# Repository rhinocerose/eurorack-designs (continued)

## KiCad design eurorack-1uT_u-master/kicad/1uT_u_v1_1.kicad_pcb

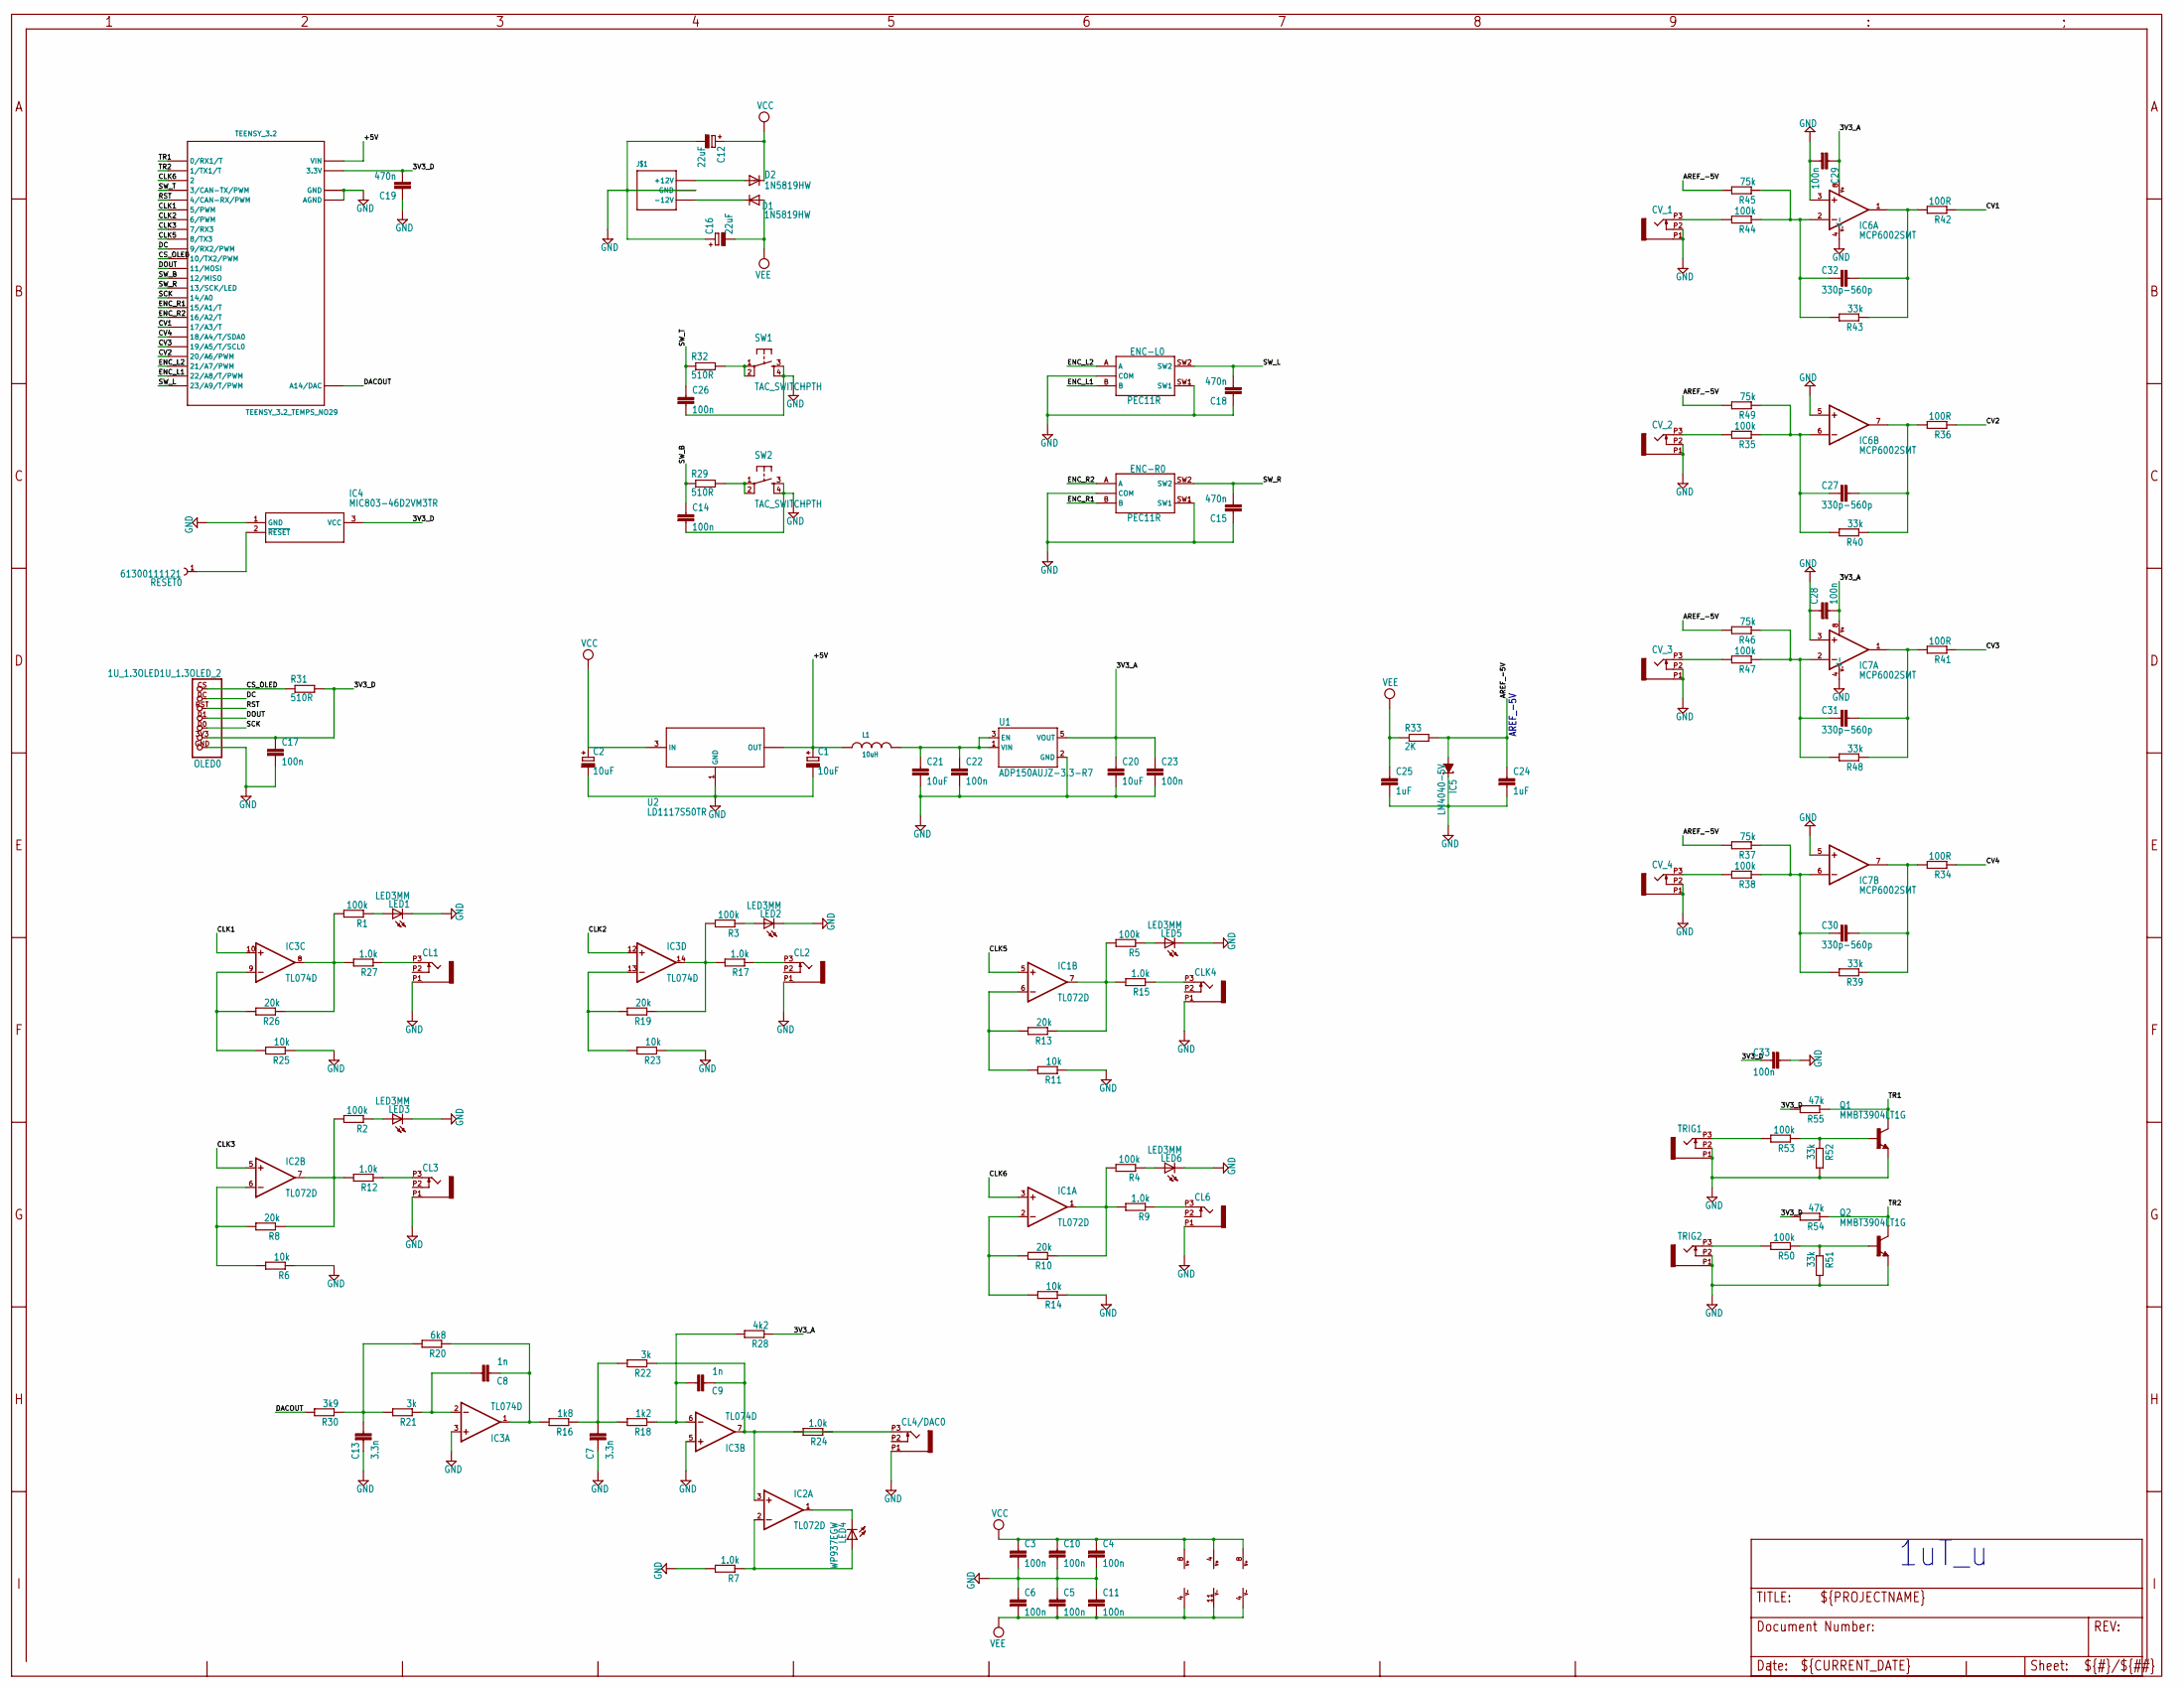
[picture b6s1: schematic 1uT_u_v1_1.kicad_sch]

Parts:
C1, C2: 10uF; PANASONIC_B
C3, C4, C5, C6, C10, C11, C14, C17, C22, C23, C26, C28, C29, C33: 100n; C0603
C7, C13: 3.3n; C0603
C8, C9: 1n; C0603
C12, C16: 22uF; PANASONIC_C
C15, C18, C19: 470n; C0603
C20, C21: 10uF; C1206K
C24, C25: 1uF; C0603
C27, C30, C31, C32: 330p-560p; C0603
CL1, CL2, CL3, CL4/DAC0, CL6: OG-PJ301_PJ301_THONKICONN; OG-PJ301_WQP_PJ_301M6_NO_HOLE
CLK4: OG-PJ301_PJ301_THONKICONN; OG-PJ301_WQP_PJ_301M6_NO_HOLE
CV_1, CV_2, CV_3, CV_4: OG-PJ301_PJ301_THONKICONN; OG-PJ301_WQP_PJ_301M6_NO_HOLE
D1, D2: 1N5819HW; DIODE_SOD123
ENC-L0: PEC11R; PEC11R-4XXXK-SXXXX
ENC-R0: PEC11R; PEC11R-4XXXK-SXXXX
IC1, IC2: TL072D; SO08
IC3: TL074D; SO14
IC4: MIC803-46D2VM3TR; SOT95P230X110-3N
IC5: LM4040-5V; DBZ_R-PDSO-G3
IC6, IC7: MCP6002SMT; SOIC8
J$1: POWER_SIMPLE10; POWER_10
L1: 10uH; WE-LQ_M
LED1, LED2, LED3, LED5, LED6: LED3MM
LED4: WP937EGW; LED3MM
OLED0: 1U_1.3OLED1U_1.3OLED_2; 1U_1.3OLED_2
Q1, Q2: MMBT3904LT1G; TRANSISTOR_SOT23-BEC
R1, R2, R3, R4, R5, R35, R38, R44, R47, R50, R53: 100k; R0603
R6, R11, R14, R23, R25: 10k; R0603
R7, R9, R12, R15, R17, R24, R27: 1.0k; R0603
R8, R10, R13, R19, R26: 20k; R0603
R16: 1k8; R0603
R18: 1k2; R0603
R20: 6k8; R0603
R21, R22: 3k; R0603
R28: 4k2; R0603
R29, R31, R32: 510R; R0603
R30: 3k9; R0603
R33: 2K; R0603
R34, R36, R41, R42: 100R; R0603
R37, R45, R46, R49: 75k; R0603
R39, R40, R43, R48, R51, R52: 33k; R0603
R54, R55: 47k; R0603
RESET0: 61300111121
SW1, SW2: TAC_SWITCHPTH; TACTILE-PTH
TEENSY_3.2: TEENSY_3.2_TEMPS_NO29
TRIG1, TRIG2: OG-PJ301_PJ301_THONKICONN; OG-PJ301_WQP_PJ_301M6_NO_HOLE
U1: ADP150AUJZ-3.3-R7; SOT95P280X100-5N
U2: LD1117S50TR; SOT223

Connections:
3V3_A: C20.1, C23.1, C28.2, C29.1, IC6.8 (V+), IC7.8 (V+), R28.1, U1.5 (VOUT)
3V3_D: C17.1, C19.2, C33.2, IC4.3 (VCC), OLED0.3V3, R31.2, R54.2, R55.2, TEENSY_3.2.3.3V
+5V: C1.+, L1.1, TEENSY_3.2.VIN, U2.2 (OUT), U2.4 (OUT)
AREF_-5V: C24.1, IC5.2 (A), R33.2, R37.2, R45.2, R46.2, R49.2
CLK1: IC3.10 (+IN), TEENSY_3.2.5 (5/PWM)
CLK2: IC3.12 (+IN), TEENSY_3.2.6 (6/PWM)
CLK3: IC2.5 (+IN), TEENSY_3.2.7 (7/RX3)
CLK5: IC1.5 (+IN), TEENSY_3.2.8 (8/TX3)
CLK6: IC1.3 (+IN), TEENSY_3.2.2
CS_OLED: OLED0.CS, R31.1, TEENSY_3.2.10 (10/TX2/PWM)
CV1: R42.1, TEENSY_3.2.17/A3 (17/A3/T)
CV2: R36.1, TEENSY_3.2.20/A6 (20/A6/PWM)
CV3: R41.1, TEENSY_3.2.19/A5 (19/A5/T/SCL0)
CV4: R34.1, TEENSY_3.2.18/A4 (18/A4/T/SDA0)
DACOUT: R30.2, TEENSY_3.2.RESET/DAC (A14/DAC)
DC: OLED0.DC, TEENSY_3.2.9 (9/RX2/PWM)
DOUT: OLED0.D1, TEENSY_3.2.11 (11/MOSI)
ENC_L1: ENC-L0.B, TEENSY_3.2.22/A8 (22/A8/T/PWM)
ENC_L2: ENC-L0.A, TEENSY_3.2.21/A7 (21/A7/PWM)
ENC_R1: ENC-R0.B, TEENSY_3.2.15/A1 (15/A1/T)
ENC_R2: ENC-R0.A, TEENSY_3.2.16/A2 (16/A2/T)
GND: C1.-, C2.-, C3.2, C4.2, C5.1, C6.1, C7.2, C10.2, C11.1, C12.-, C13.2, C14.2, C15.1, C16.+, C17.2, C18.1, C19.1, C20.2, C21.2, C22.2, C23.2, C24.2, C25.2, C26.2, C28.1, C29.2, C33.1, CL1.P1 (1), CL2.P1 (1), CL3.P1 (1), CL4/DAC0.P1 (1), CL6.P1 (1), CLK4.P1 (1), CV_1.P1 (1), CV_1.P2 (2), CV_2.P1 (1), CV_2.P2 (2), CV_3.P1 (1), CV_3.P2 (2), CV_4.P1 (1), CV_4.P2 (2), ENC-L0.C (COM), ENC-L0.SH1 (COM), ENC-L0.SH2 (COM), ENC-L0.SW1, ENC-R0.C (COM), ENC-R0.SH1 (COM), ENC-R0.SH2 (COM), ENC-R0.SW1, IC3.3 (+IN), IC3.5 (+IN), IC4.1 (GND), IC5.1 (C), IC6.3 (+IN), IC6.4 (V-), IC6.5 (+IN), IC7.3 (+IN), IC7.4 (V-), IC7.5 (+IN), J$1.3 (GND), J$1.4 (GND), J$1.5 (GND), J$1.6 (GND), J$1.7 (GND), J$1.8 (GND), LED1.K (C), LED2.K (C), LED3.K (C), LED5.K (C), LED6.K (C), OLED0.GND, Q1.E, Q2.E, R6.1, R7.2, R11.1, R14.1, R23.1, R25.1, R51.2, R52.2, SW1.3, SW1.4, SW2.3, SW2.4, TEENSY_3.2.AGND, TEENSY_3.2.GND, TRIG1.P1 (1), TRIG1.P2 (2), TRIG2.P1 (1), TRIG2.P2 (2), U1.2 (GND), U2.1 (GND)
unnamed: D2.A, J$1.9 (+12V), J$1.10 (+12V)
unnamed: C21.1, C22.1, L1.2, U1.1 (VIN), U1.3 (EN)
unnamed: CV_1.P3 (3), R44.2
unnamed: C32.2, IC6.2 (-IN), R43.2, R44.1, R45.1
unnamed: C32.1, IC6.1 (OUT), R42.2, R43.1
unnamed: R32.2, SW1.1, SW1.2
unnamed: CV_2.P3 (3), R35.2
unnamed: R29.2, SW2.1, SW2.2
unnamed: C27.2, IC6.6 (-IN), R35.1, R40.2, R49.1
unnamed: C27.1, IC6.7 (OUT), R36.2, R40.1
unnamed: CV_3.P3 (3), R47.2
unnamed: C31.2, IC7.2 (-IN), R46.1, R47.1, R48.2
unnamed: C31.1, IC7.1 (OUT), R41.2, R48.1
unnamed: CV_4.P3 (3), R38.2
unnamed: C30.2, IC7.6 (-IN), R37.1, R38.1, R39.2
unnamed: C30.1, IC7.7 (OUT), R34.2, R39.1
unnamed: R53.2, TRIG1.P3 (3)
unnamed: Q1.B, R52.1, R53.1
unnamed: R50.2, TRIG2.P3 (3)
unnamed: Q2.B, R50.1, R51.1
unnamed: CL1.P3 (3), R27.1
unnamed: CL3.P3 (3), R12.1
unnamed: IC1.6 (-IN), R11.2, R13.2
unnamed: IC1.7 (OUT), R5.2, R13.1, R15.2
unnamed: IC3.13 (-IN), R19.2, R23.2
unnamed: IC3.9 (-IN), R25.2, R26.2
unnamed: IC3.8 (OUT), R1.2, R26.1, R27.2
unnamed: CLK4.P3 (3), R15.1
unnamed: IC3.14 (OUT), R3.2, R17.2, R19.1
unnamed: CL2.P3 (3), R17.1
unnamed: IC2.6 (-IN), R6.2, R8.2
unnamed: IC2.7 (OUT), R2.2, R8.1, R12.2
unnamed: IC1.2 (-IN), R10.2, R14.2
unnamed: IC2.1 (OUT), LED4.K (C)
unnamed: IC2.2 (-IN), LED4.A, R7.1
unnamed: IC1.1 (OUT), R4.2, R9.2, R10.1
unnamed: CL6.P3 (3), R9.1
unnamed: D1.C, J$1.1 (-12V), J$1.2 (-12V)
unnamed: C13.1, R20.2, R21.2, R30.1
unnamed: C8.1, IC3.2 (-IN), R21.1
unnamed: C8.2, IC3.1 (OUT), R16.2, R20.1
unnamed: C7.1, R16.1, R18.2, R22.2
unnamed: C9.1, IC3.6 (-IN), R18.1, R28.2
unnamed: LED3.A, R2.1
unnamed: LED1.A, R1.1
unnamed: LED2.A, R3.1
unnamed: LED5.A, R5.1
unnamed: LED6.A, R4.1
unnamed: IC4.2 (~RESET), RESET0.1
RST: OLED0.RST, TEENSY_3.2.4 (4/CAN-RX/PWM)
SCK: OLED0.D0, TEENSY_3.2.14/A0
SW_B: C14.1, R29.1, TEENSY_3.2.12 (12/MISO)
SW_L: C18.2, ENC-L0.SW2, TEENSY_3.2.23/A9 (23/A9/T/PWM)
SW_R: C15.2, ENC-R0.SW2, TEENSY_3.2.13 (13/SCK/LED)
SW_T: C26.1, R32.1, TEENSY_3.2.3 (3/CAN-TX/PWM)
TR1: Q1.C, R55.1, TEENSY_3.2.0 (0/RX1/T)
TR2: Q2.C, R54.1, TEENSY_3.2.1 (1/TX1/T)
VCC: C2.+, C3.1, C4.1, C10.1, C12.+, D2.C, IC1.8 (V+), IC2.8 (V+), IC3.4 (V+), U2.3 (IN)
VEE: C5.2, C6.2, C11.2, C16.-, C25.1, D1.A, IC1.4 (V-), IC2.4 (V-), IC3.11 (V-), R33.1

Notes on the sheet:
1uT_u
AREF_-5V

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
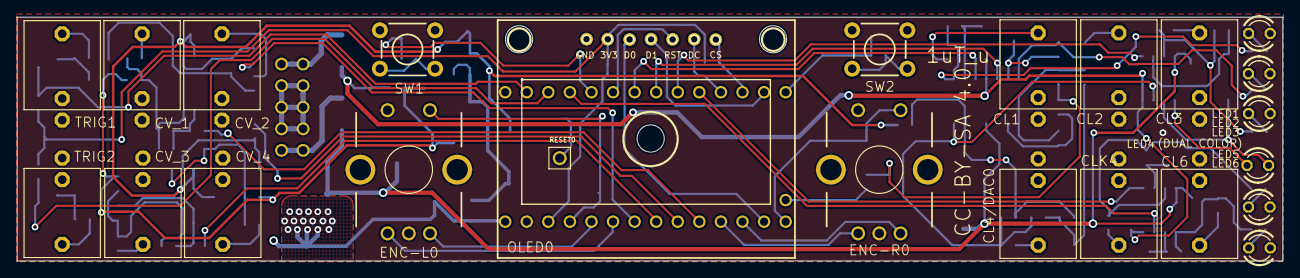
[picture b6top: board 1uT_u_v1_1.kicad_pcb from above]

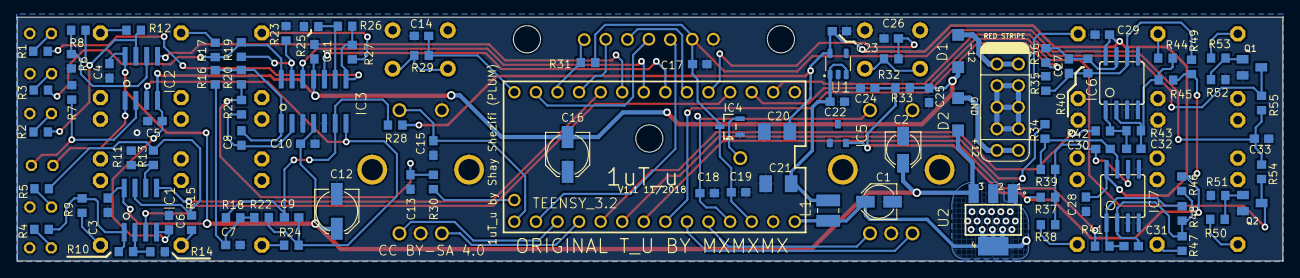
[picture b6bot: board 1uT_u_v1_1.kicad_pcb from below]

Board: 2 copper layers, 149.0 x 28.7 mm, 128 parts (104 on the bottom side), 83 nets.

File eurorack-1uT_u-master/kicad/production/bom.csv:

Designator,Footprint,Quantity,Value,LCSC Part #
"C1, C2",PANASONIC_B_334,2,10uF,
"C10, C11, C14, C17, C22, C23, C26, C28, C29, C3, C33, C4, C5, C6",C0603_348,14,100n,
"C12, C16",PANASONIC_C_334,2,22uF,
"C13, C7",C0603_348,2,3.3n,
"C15, C18, C19",C0603_348,3,470n,
"C20, C21",C1206K_348,2,10uF,
"C24, C25",C0603_348,2,1uF,
"C27, C30, C31, C32",C0603_348,4,330p-560p,
"C8, C9",C0603_348,2,1n,
"CL1, CL2, CL3, CL4/DAC0, CL6, CLK4, CV_1, CV_2, CV_3, CV_4, TRIG1, TRIG2",OG-PJ301_WQP_PJ_301M6_NO_HOLE,12,OG-PJ301_PJ301_THONKICONN,
"D1, D2",DIODE_SOD123,2,1N5819HW,
"ENC-L0, ENC-R0",PEC11R-4XXXK-SXXXX,2,PEC11R,
"IC1, IC2",SO08_262,2,TL072D,
IC3,SO14_262,1,TL074D,
IC4,SOT95P230X110-3N,1,MIC803-46D2VM3TR,
IC5,DBZ_R-PDSO-G3_387,1,LM4040-5V,
"IC6, IC7",SOIC8,2,MCP6002SMT,
J$1,POWER_10,1,POWER_SIMPLE10,
L1,WE-LQ_M_448,1,10uH,
"LED1, LED2, LED3, LED5, LED6",LED3MM_259,5,,
LED4,LED3MM_259,1,WP937EGW,
OLED0,1U_1.3OLED_2,1,1U_1.3OLED1U_1.3OLED_2,
"Q1, Q2",TRANSISTOR_SOT23-BEC,2,MMBT3904LT1G,
"R1, R2, R3, R35, R38, R4, R44, R47, R5, R50, R53",R0603_334,11,100k,
"R10, R13, R19, R26, R8",R0603_334,5,20k,
"R11, R14, R23, R25, R6",R0603_334,5,10k,
"R12, R15, R17, R24, R27, R7, R9",R0603_334,7,1.0k,
R16,R0603_334,1,1k8,
R18,R0603_334,1,1k2,
R20,R0603_334,1,6k8,
"R21, R22",R0603_334,2,3k,
R28,R0603_334,1,4k2,
"R29, R31, R32",R0603_334,3,510R,
R30,R0603_334,1,3k9,
R33,R0603_334,1,2K,
"R34, R36, R41, R42",R0603_334,4,100R,
"R37, R45, R46, R49",R0603_334,4,75k,
"R39, R40, R43, R48, R51, R52",R0603_334,6,33k,
"R54, R55",R0603_334,2,47k,
RESET0,61300111121_479,1,,
"SW1, SW2",TACTILE-PTH,2,,
TEENSY_3.2,TEENSY_3.2_TEMPS_NO29,1,TEENSY_3.2_TEMPS_NO29,
U1,SOT95P280X100-5N,1,ADP150AUJZ-3.3-R7,
U2,SOT223,1,LD1117S50TR,

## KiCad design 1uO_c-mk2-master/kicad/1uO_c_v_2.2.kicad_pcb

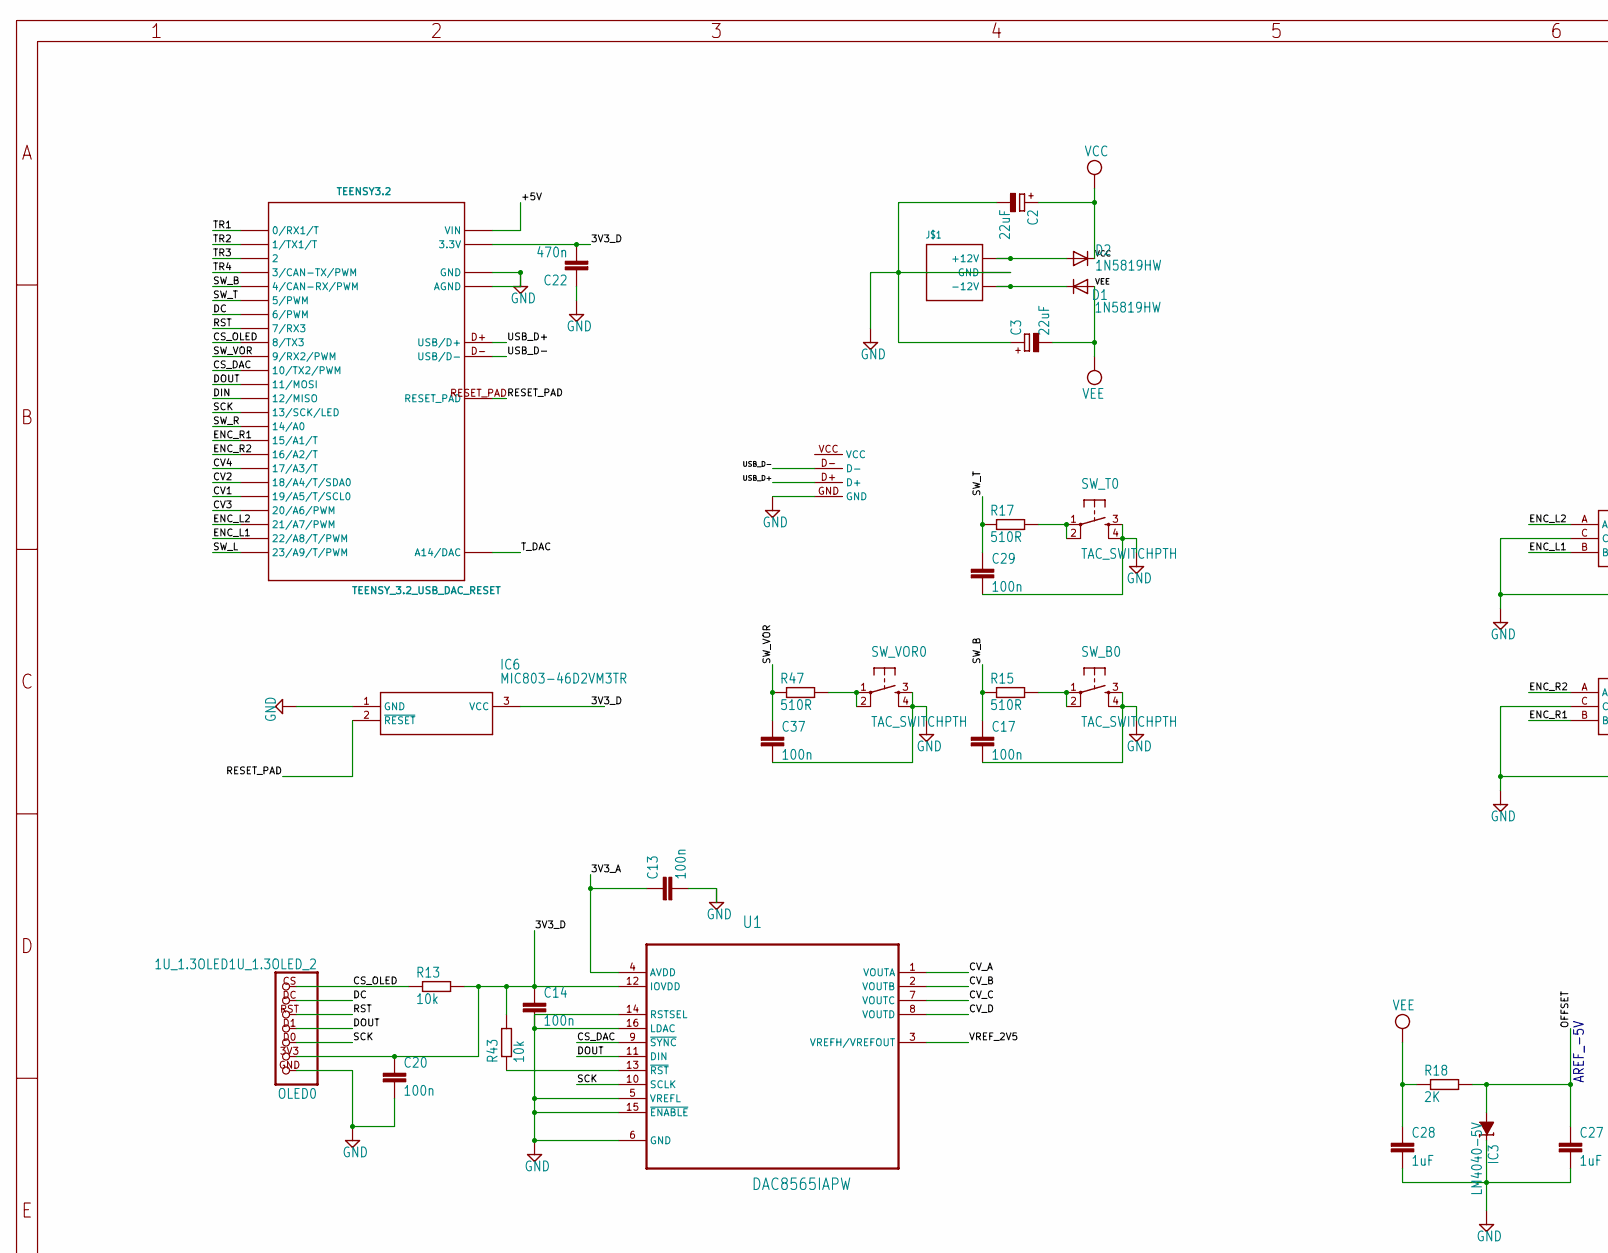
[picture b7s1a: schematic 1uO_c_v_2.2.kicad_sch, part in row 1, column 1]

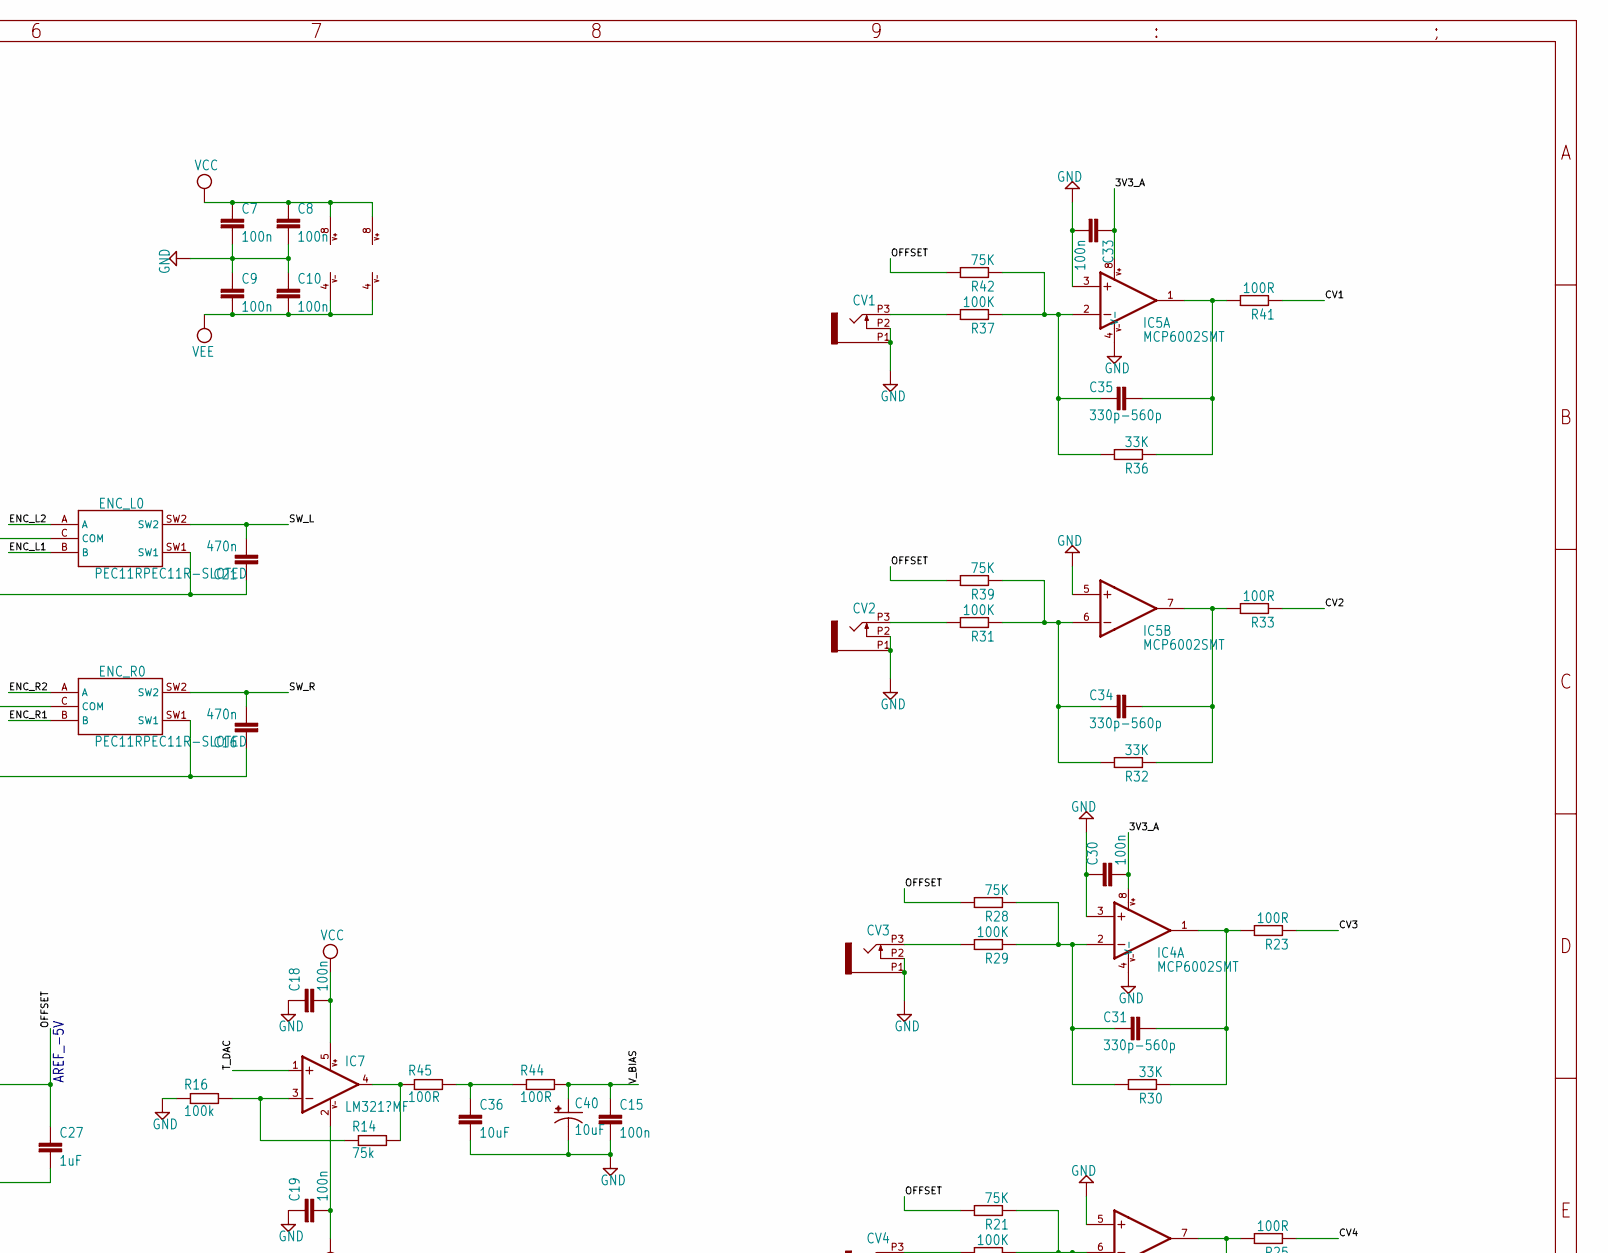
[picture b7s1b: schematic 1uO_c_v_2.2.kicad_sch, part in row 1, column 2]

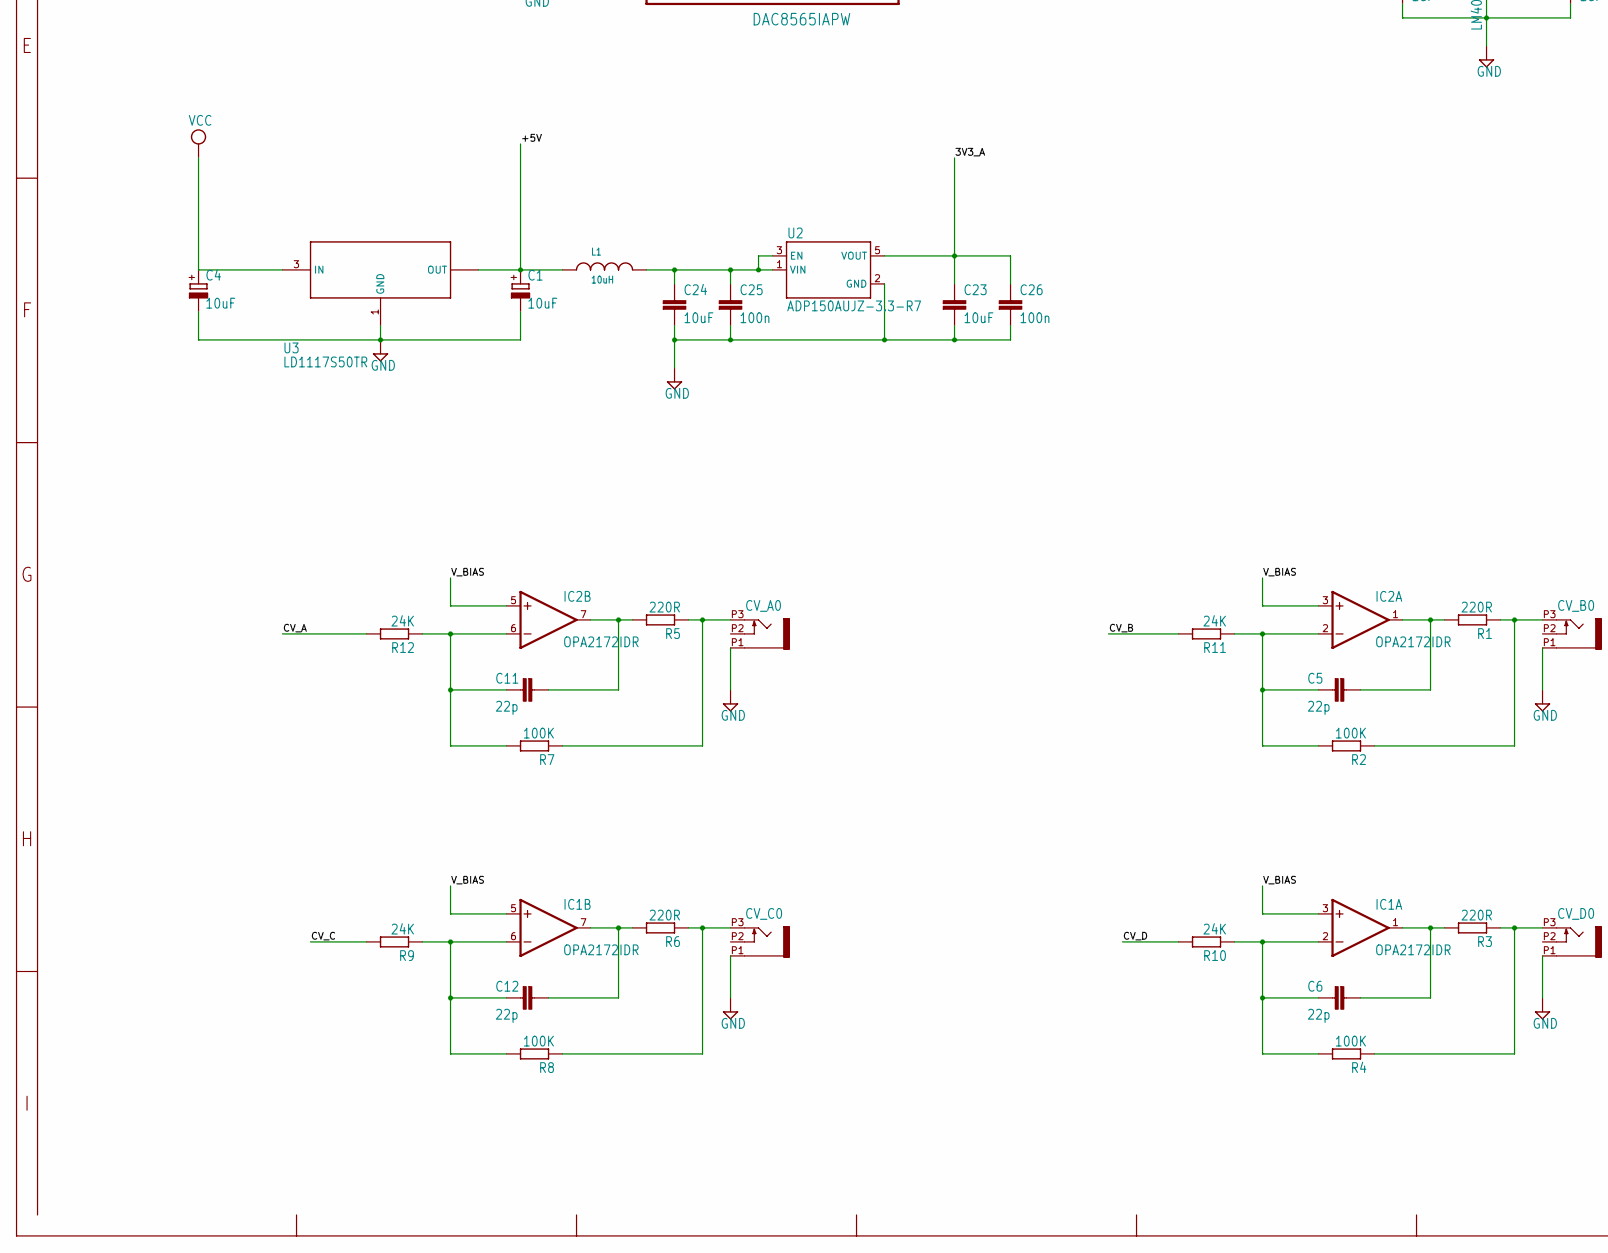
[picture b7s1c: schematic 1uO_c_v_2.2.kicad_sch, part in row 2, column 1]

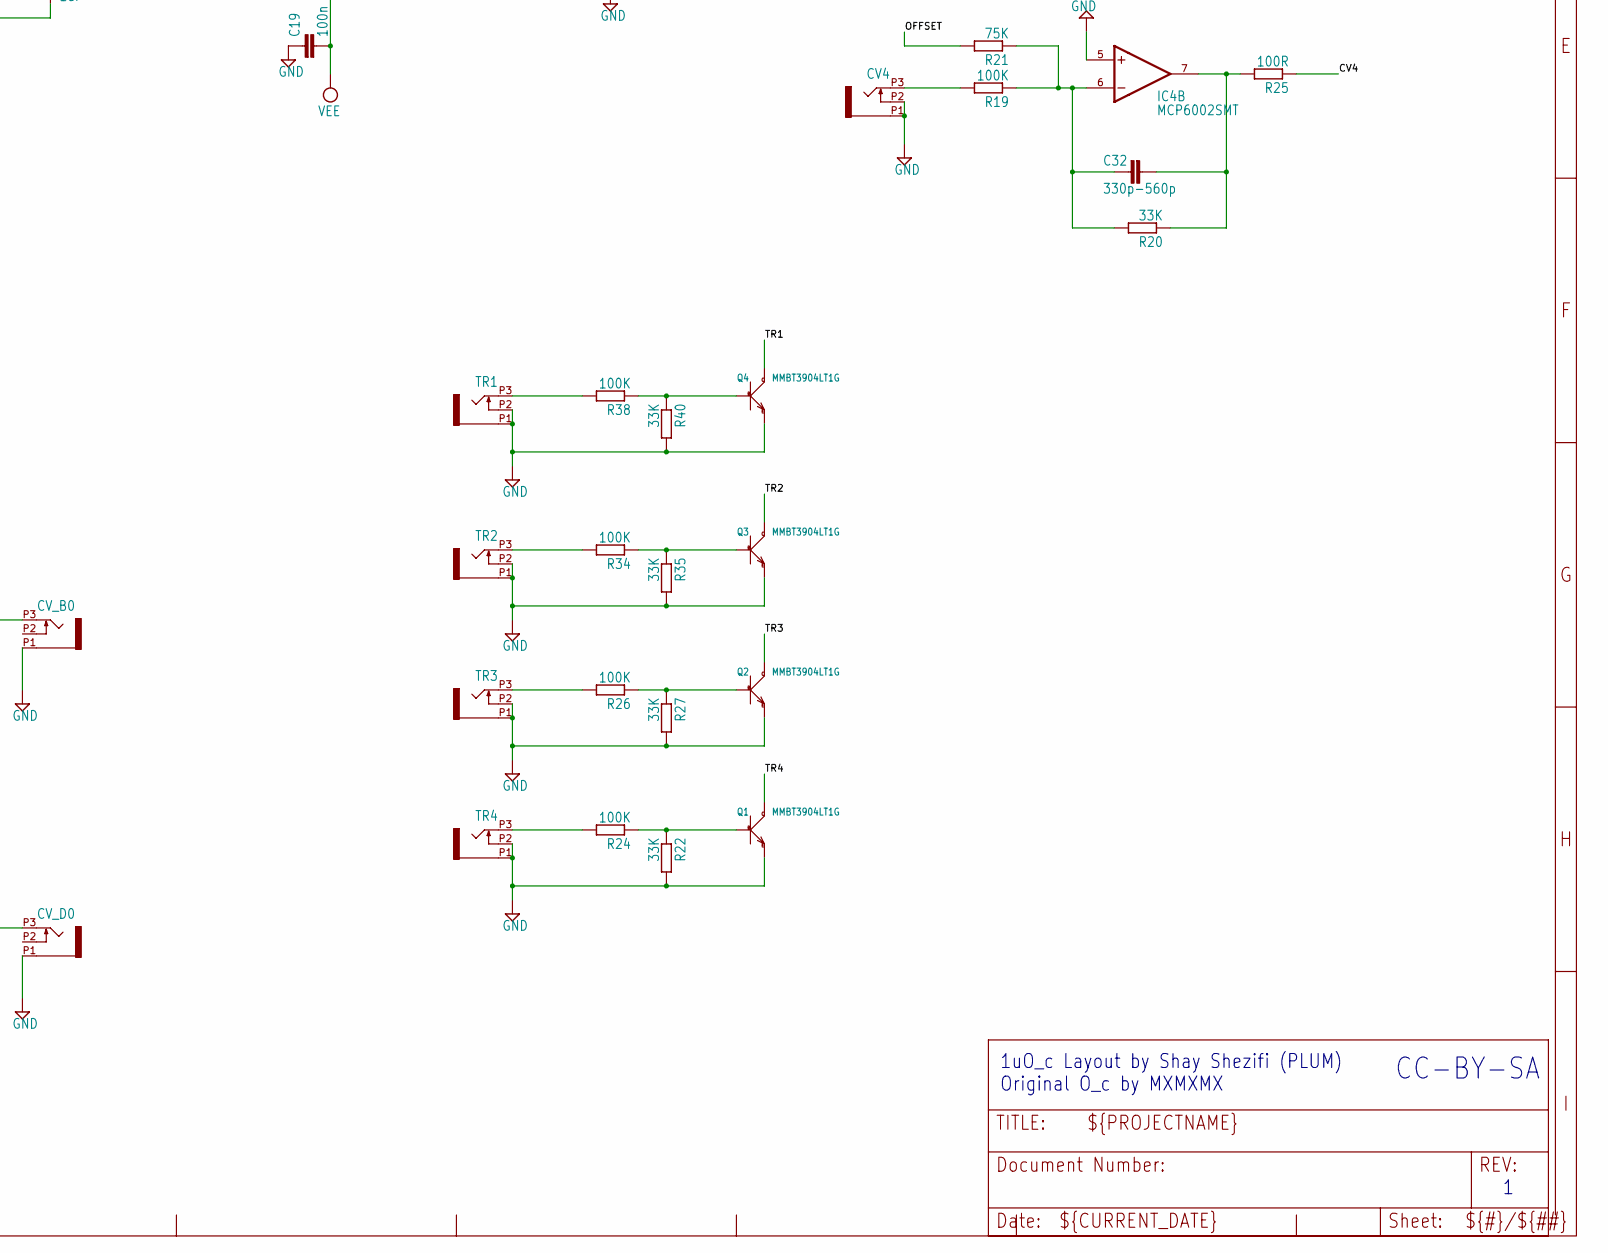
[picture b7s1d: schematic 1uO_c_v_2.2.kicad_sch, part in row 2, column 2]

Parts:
C1, C4: 10uF; PANASONIC_B
C2, C3: 22uF; PANASONIC_C
C5, C6, C11, C12: 22p; C0603
C7, C8, C9, C10, C13, C14, C15, C17, C18, C19, C20, C25, C26, C29, C30, C33, C37: 100n; C0603
C16, C21, C22: 470n; C0603
C23, C24: 10uF; C1206K
C27, C28: 1uF; C0603
C31, C32, C34, C35: 330p-560p; C0603
C36: 10uF; C0603
C40: 10uF; PANASONIC_A
CV1, CV2, CV3, CV4: OG-PJ301_PJ301_THONKICONN; OG-PJ301_WQP_PJ_301M6_NO_HOLE
CV_A0: OG-PJ301_PJ301_THONKICONN; OG-PJ301_WQP_PJ_301M6_NO_HOLE
CV_B0: OG-PJ301_PJ301_THONKICONN; OG-PJ301_WQP_PJ_301M6_NO_HOLE
CV_C0: OG-PJ301_PJ301_THONKICONN; OG-PJ301_WQP_PJ_301M6_NO_HOLE
CV_D0: OG-PJ301_PJ301_THONKICONN; OG-PJ301_WQP_PJ_301M6_NO_HOLE
D1, D2: 1N5819HW; DIODE_SOD123
ENC_L0: PEC11RPEC11R-SLOTED; PEC11R-SLOTED
ENC_R0: PEC11RPEC11R-SLOTED; PEC11R-SLOTED
IC1, IC2: OPA2172IDR; SO08
IC3: LM4040-5V; DBZ_R-PDSO-G3
IC4, IC5: MCP6002SMT; SOIC8
IC6: MIC803-46D2VM3TR; SOT95P230X110-3N
IC7: LM321?MF; SOT23-5
J$1: POWER_SIMPLE10; POWER_10
L1: 10uH; WE-LQ_M
OLED0: 1U_1.3OLED1U_1.3OLED_2; 1U_1.3OLED_2
Q1, Q2, Q3, Q4: MMBT3904LT1G; SOT-23
R1, R3, R5, R6: 220R; R0603
R2, R4, R7, R8, R19, R24, R26, R29, R31, R34, R37, R38: 100K; R0603
R9, R10, R11, R12: 24K; R0603
R13, R43: 10k; R0603
R14: 75k; R0603
R15, R17, R47: 510R; R0603
R16: 100k; R0603
R18: 2K; R0603
R20, R22, R27, R30, R32, R35, R36, R40: 33K; R0603
R21, R28, R39, R42: 75K; R0603
R23, R25, R33, R41, R44, R45: 100R; R0603
SW_B0: TAC_SWITCHPTH; TACTILE-PTH
SW_T0: TAC_SWITCHPTH; TACTILE-PTH
SW_VOR0: TAC_SWITCHPTH; TACTILE-PTH
TEENSY3.2: TEENSY_3.2_USB_DAC_RESET
TR1, TR2, TR3, TR4: OG-PJ301_PJ301_THONKICONN; OG-PJ301_WQP_PJ_301M6_NO_HOLE
U1: DAC8565IAPW; SOP65P640X120-16N
U2: ADP150AUJZ-3.3-R7; SOT95P280X100-5N
U3: LD1117S50TR; SOT223
U$1: USB_BOARD; MICRO-USB-BOARD

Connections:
3V3_A: C13.1, C23.1, C26.1, C30.2, C33.1, IC4.8 (V+), IC5.8 (V+), U1.4 (AVDD), U2.5 (VOUT)
3V3_D: C14.1, C20.1, C22.2, IC6.3 (VCC), OLED0.3V3, R13.2, R43.2, TEENSY3.2.3.3V, U1.12 (IOVDD)
+5V: C1.+, L1.1, TEENSY3.2.VIN, U3.2 (OUT), U3.4 (OUT)
CS_DAC: TEENSY3.2.10 (10/TX2/PWM), U1.9 (~SYNC)
CS_OLED: OLED0.CS, R13.1, TEENSY3.2.8 (8/TX3)
CV1: R41.1, TEENSY3.2.19/A5 (19/A5/T/SCL0)
CV2: R33.1, TEENSY3.2.18/A4 (18/A4/T/SDA0)
CV3: R23.1, TEENSY3.2.20/A6 (20/A6/PWM)
CV4: R25.1, TEENSY3.2.17/A3 (17/A3/T)
CV_A: R12.2, U1.1 (VOUTA)
CV_B: R11.2, U1.2 (VOUTB)
CV_C: R9.2, U1.7 (VOUTC)
CV_D: R10.2, U1.8 (VOUTD)
DC: OLED0.DC, TEENSY3.2.6 (6/PWM)
DIN: TEENSY3.2.12 (12/MISO)
DOUT: OLED0.D1, TEENSY3.2.11 (11/MOSI), U1.11 (DIN)
ENC_L1: ENC_L0.B, TEENSY3.2.22/A8 (22/A8/T/PWM)
ENC_L2: ENC_L0.A, TEENSY3.2.21/A7 (21/A7/PWM)
ENC_R1: ENC_R0.B, TEENSY3.2.15/A1 (15/A1/T)
ENC_R2: ENC_R0.A, TEENSY3.2.16/A2 (16/A2/T)
GND: C1.-, C2.-, C3.+, C4.-, C7.2, C8.2, C9.1, C10.1, C13.2, C14.2, C15.2, C16.1, C17.2, C18.1, C19.1, C20.2, C21.1, C22.1, C23.2, C24.2, C25.2, C26.2, C27.2, C28.2, C29.2, C30.1, C33.2, C36.2, C37.2, C40.-, CV1.P1 (1), CV1.P2 (2), CV2.P1 (1), CV2.P2 (2), CV3.P1 (1), CV3.P2 (2), CV4.P1 (1), CV4.P2 (2), CV_A0.P1 (1), CV_B0.P1 (1), CV_C0.P1 (1), CV_D0.P1 (1), ENC_L0.C (COM), ENC_L0.SW1, ENC_R0.C (COM), ENC_R0.SW1, IC3.1 (C), IC4.3 (+IN), IC4.4 (V-), IC4.5 (+IN), IC5.3 (+IN), IC5.4 (V-), IC5.5 (+IN), IC6.1 (GND), J$1.3 (GND), J$1.4 (GND), J$1.5 (GND), J$1.6 (GND), J$1.7 (GND), J$1.8 (GND), OLED0.GND, Q1.2 (E), Q2.2 (E), Q3.2 (E), Q4.2 (E), R16.1, R22.2, R27.2, R35.2, R40.2, SW_B0.3, SW_B0.4, SW_T0.3, SW_T0.4, SW_VOR0.3, SW_VOR0.4, TEENSY3.2.AGND, TEENSY3.2.GND, TR1.P1 (1), TR1.P2 (2), TR2.P1 (1), TR2.P2 (2), TR3.P1 (1), TR3.P2 (2), TR4.P1 (1), TR4.P2 (2), U1.5 (VREFL), U1.6 (GND), U1.14 (RSTSEL), U1.15 (~ENABLE), U1.16 (LDAC), U2.2 (GND), U3.1 (GND), U$1.GND
unnamed: D1.C, J$1.1 (-12V), J$1.2 (-12V)
unnamed: D2.A, J$1.9 (+12V), J$1.10 (+12V)
unnamed: C24.1, C25.1, L1.2, U2.1 (VIN), U2.3 (EN)
unnamed: CV1.P3 (3), R37.2
unnamed: C35.2, IC5.2 (-IN), R36.2, R37.1, R42.1
unnamed: C35.1, IC5.1 (OUT), R36.1, R41.2
unnamed: R17.2, SW_T0.1, SW_T0.2
unnamed: CV2.P3 (3), R31.2
unnamed: R15.2, SW_B0.1, SW_B0.2
unnamed: C34.2, IC5.6 (-IN), R31.1, R32.2, R39.1
unnamed: C34.1, IC5.7 (OUT), R32.1, R33.2
unnamed: CV3.P3 (3), R29.2
unnamed: C31.2, IC4.2 (-IN), R28.1, R29.1, R30.2
unnamed: C31.1, IC4.1 (OUT), R23.2, R30.1
unnamed: CV4.P3 (3), R19.2
unnamed: C32.2, IC4.6 (-IN), R19.1, R20.2, R21.1
unnamed: C32.1, IC4.7 (OUT), R20.1, R25.2
unnamed: R38.2, TR1.P3 (3)
unnamed: Q4.1 (B), R38.1, R40.1
unnamed: R34.2, TR2.P3 (3)
unnamed: Q3.1 (B), R34.1, R35.1
unnamed: R26.2, TR3.P3 (3)
unnamed: Q2.1 (B), R26.1, R27.1
unnamed: R24.2, TR4.P3 (3)
unnamed: Q1.1 (B), R22.1, R24.1
unnamed: C5.2, IC2.2 (-IN), R2.2, R11.1
unnamed: C11.2, IC2.6 (-IN), R7.2, R12.1
unnamed: C11.1, IC2.7 (OUT), R5.2
unnamed: CV_A0.P3 (3), R5.1, R7.1
unnamed: C5.1, IC2.1 (OUT), R1.2
unnamed: CV_B0.P3 (3), R1.1, R2.1
unnamed: C12.2, IC1.6 (-IN), R8.2, R9.1
unnamed: C12.1, IC1.7 (OUT), R6.2
unnamed: CV_C0.P3 (3), R6.1, R8.1
unnamed: C6.2, IC1.2 (-IN), R4.2, R10.1
unnamed: C6.1, IC1.1 (OUT), R3.2
unnamed: CV_D0.P3 (3), R3.1, R4.1
unnamed: R43.1, U1.13 (~RST)
unnamed: IC7.3 (-IN), R14.1, R16.2
unnamed: IC7.4 (OUT), R14.2, R45.1
unnamed: C36.1, R44.1, R45.2
unnamed: R47.2, SW_VOR0.1, SW_VOR0.2
OFFSET: C27.1, IC3.2 (A), R18.2, R21.2, R28.2, R39.2, R42.2
RESET_PAD: IC6.2 (~RESET), TEENSY3.2.RESET_PAD
RST: OLED0.RST, TEENSY3.2.7 (7/RX3)
SCK: OLED0.D0, TEENSY3.2.13 (13/SCK/LED), U1.10 (SCLK)
SW_B: C17.1, R15.1, TEENSY3.2.4 (4/CAN-RX/PWM)
SW_L: C21.2, ENC_L0.SW2, TEENSY3.2.23/A9 (23/A9/T/PWM)
SW_R: C16.2, ENC_R0.SW2, TEENSY3.2.14/A0
SW_T: C29.1, R17.1, TEENSY3.2.5 (5/PWM)
SW_VOR: C37.1, R47.1, TEENSY3.2.9 (9/RX2/PWM)
TR1: Q4.3 (C), TEENSY3.2.0 (0/RX1/T)
TR2: Q3.3 (C), TEENSY3.2.1 (1/TX1/T)
TR3: Q2.3 (C), TEENSY3.2.2
TR4: Q1.3 (C), TEENSY3.2.3 (3/CAN-TX/PWM)
T_DAC: IC7.1 (+IN), TEENSY3.2.RESET/DAC (A14/DAC)
USB_D+: TEENSY3.2.D+ (USB/D+), U$1.D+
USB_D-: TEENSY3.2.D- (USB/D-), U$1.D-
VCC: C2.+, C4.+, C7.1, C8.1, C18.2, D2.C, IC1.8 (V+), IC2.8 (V+), IC7.5 (V+), U3.3 (IN)
VEE: C3.-, C9.2, C10.2, C19.2, C28.1, D1.A, IC1.4 (V-), IC2.4 (V-), IC7.2 (V-), R18.1
VREF_2V5: U1.3 (VREFH/VREFOUT)
V_BIAS: C15.1, C40.+, IC1.3 (+IN), IC1.5 (+IN), IC2.3 (+IN), IC2.5 (+IN), R44.2

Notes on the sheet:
1uO_c Layout by Shay Shezifi (PLUM) Original O_c by MXMXMX
AREF_-5V
CC-BY-SA

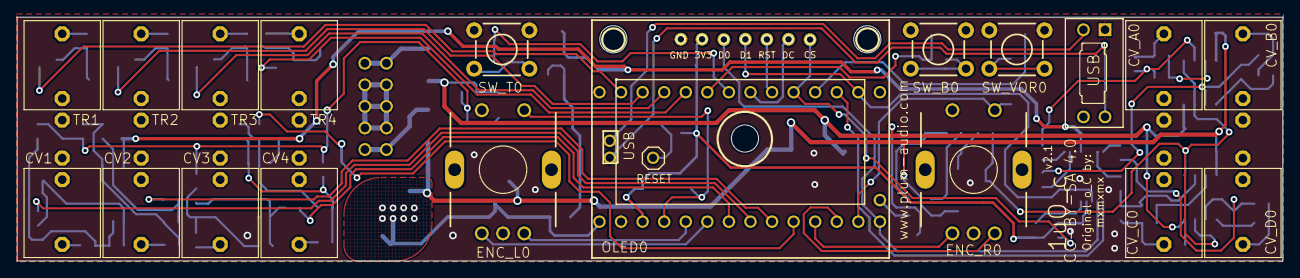
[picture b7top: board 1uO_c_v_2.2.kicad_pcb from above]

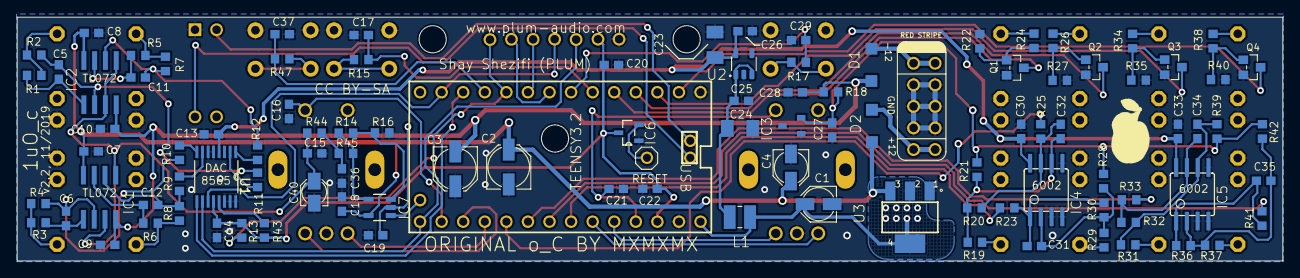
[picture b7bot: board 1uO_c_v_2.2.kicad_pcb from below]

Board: 2 copper layers, 149.0 x 28.7 mm, 122 parts (103 on the bottom side), 81 nets.

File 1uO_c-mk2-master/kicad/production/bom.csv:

Designator,Footprint,Quantity,Value,LCSC Part #
"C1, C4",PANASONIC_B_334,2,10uF,
"C10, C13, C14, C15, C17, C18, C19, C20, C25, C26, C29, C30, C33, C37, C7, C8, C9",C0603_348,17,100n,
"C11, C12, C5, C6",C0603_348,4,22p,
"C16, C21, C22",C0603_348,3,470n,
"C2, C3",PANASONIC_C_334,2,22uF,
"C23, C24",C1206K_348,2,10uF,
"C27, C28",C0603_348,2,1uF,
"C31, C32, C34, C35",C0603_348,4,330p-560p,
C36,C0603_348,1,10uF,
C40,PANASONIC_A,1,10uF,
"CV1, CV2, CV3, CV4, CV_A0, CV_B0, CV_C0, CV_D0, TR1, TR2, TR3, TR4",OG-PJ301_WQP_PJ_301M6_NO_HOLE,12,OG-PJ301_PJ301_THONKICONN,
"D1, D2",DIODE_SOD123,2,1N5819HW,
"ENC_L0, ENC_R0",PEC11R-SLOTED,2,PEC11RPEC11R-SLOTED,
"IC1, IC2",SO08_262,2,OPA2172IDR,
IC3,DBZ_R-PDSO-G3,1,LM4040-5V,
"IC4, IC5",SOIC8,2,MCP6002SMT,
IC6,SOT95P230X110-3N,1,MIC803-46D2VM3TR,
IC7,SOT23-5_262,1,LM321MF,
J$1,POWER_10,1,POWER_SIMPLE10,
L1,WE-LQ_M_448,1,10uH,
OLED0,1U_1.3OLED_2,1,1U_1.3OLED1U_1.3OLED_2,
"Q1, Q2, Q3, Q4",SOT-23_477,4,MMBT3904LT1G,
"R1, R3, R5, R6",R0603_334,4,220R,
"R10, R11, R12, R9",R0603_334,4,24K,
"R13, R43",R0603_334,2,10k,
"R14, R21, R28, R39, R42",R0603_334,5,75k,
"R15, R17, R47",R0603_334,3,510R,
"R16, R19, R2, R24, R26, R29, R31, R34, R37, R38, R4, R7, R8",R0603_334,13,100k,
R18,R0603_334,1,2K,
"R20, R22, R27, R30, R32, R35, R36, R40",R0603_334,8,33K,
"R23, R25, R33, R41, R44, R45",R0603_334,6,100R,
"SW_B0, SW_T0, SW_VOR0",TACTILE-PTH,3,,
TEENSY3.2,TEENSY_3.2_USB_DAC_RESET,1,TEENSY_3.2_USB_DAC_RESET,
U$1,MICRO-USB-BOARD,1,USB_BOARD,
U1,SOP65P640X120-16N,1,DAC8565IAPW,
U2,SOT95P280X100-5N,1,ADP150AUJZ-3.3-R7,
U3,SOT223,1,LD1117S50TR,
